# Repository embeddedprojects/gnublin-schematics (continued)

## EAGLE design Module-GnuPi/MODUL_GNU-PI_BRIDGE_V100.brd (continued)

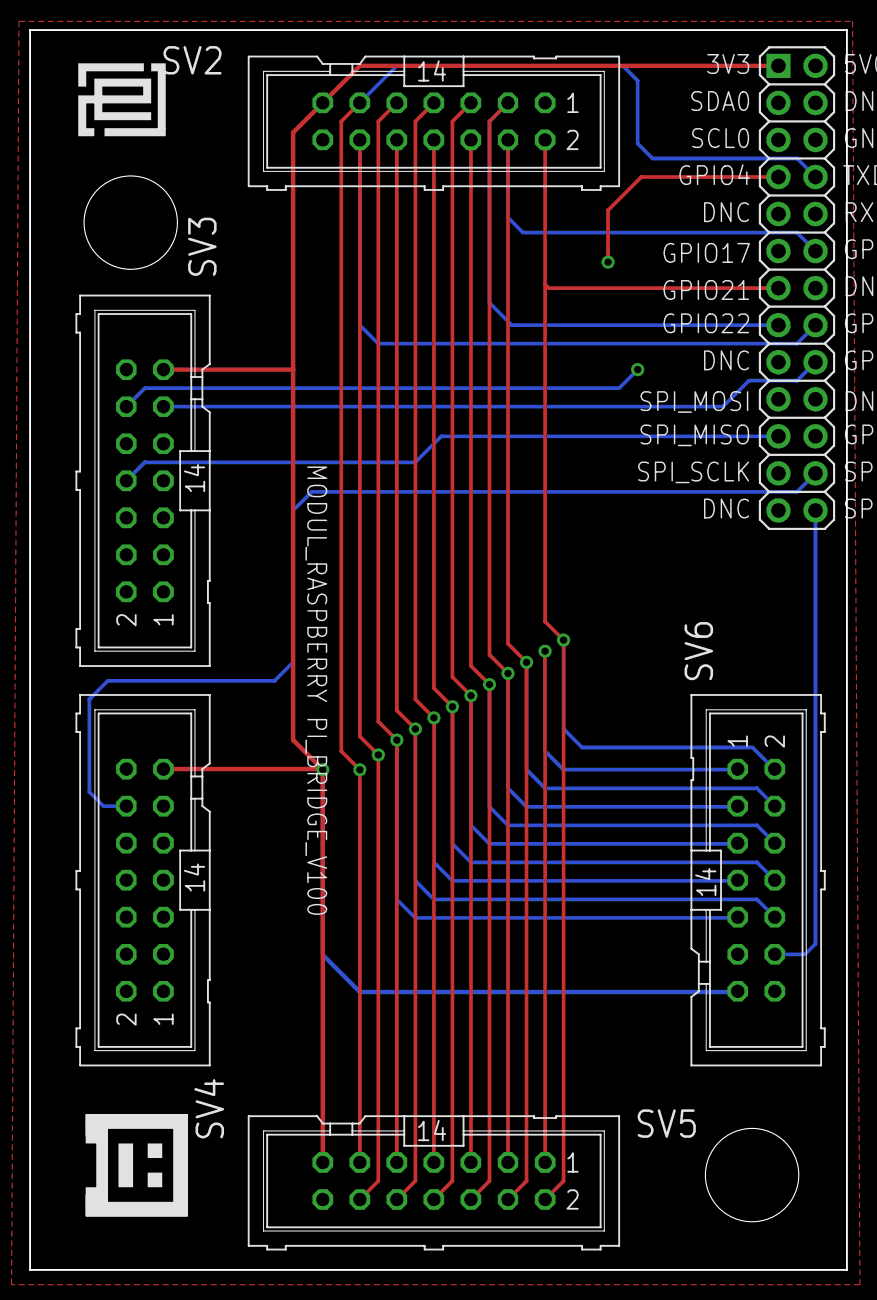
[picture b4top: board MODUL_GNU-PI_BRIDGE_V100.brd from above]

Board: 4 copper layers, 56.0 x 85.0 mm, 8 parts (0 on the bottom side), 20 nets.

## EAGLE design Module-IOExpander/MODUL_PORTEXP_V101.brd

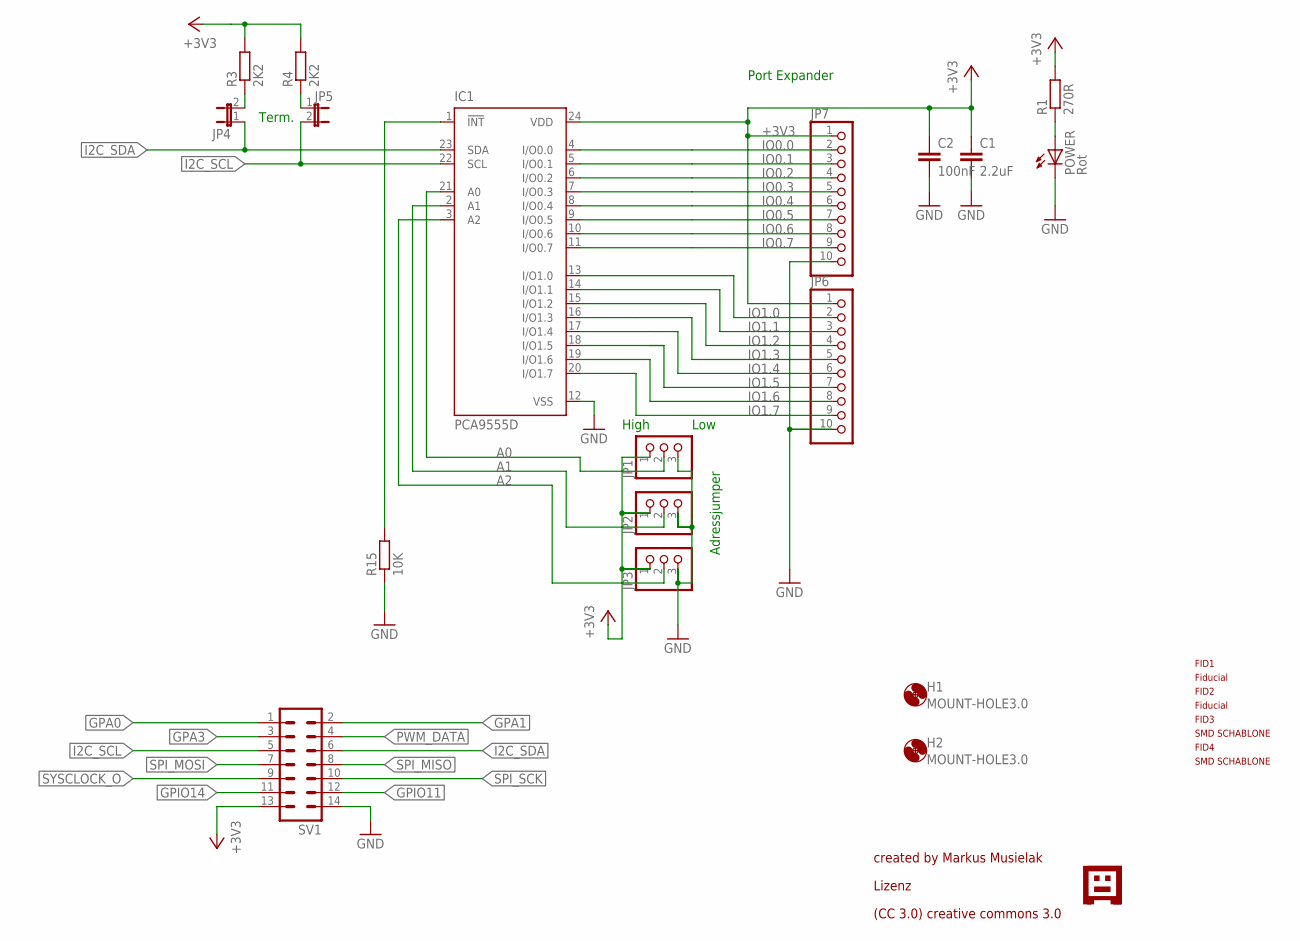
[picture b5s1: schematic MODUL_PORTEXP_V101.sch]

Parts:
C1: 2.2uF; C0805
C2: 100nF; C0805
FID1, FID2, FID3, FID4: PASSERMARKEN_FIDUCIAL
H1, H2: MOUNT-HOLE3.0; 3,0
IC1: PCA9555D; SO24
JP1, JP2, JP3: PINHD-1X3; 1X03
JP4, JP5: JP1E; JP1
JP6, JP7: PINHD-1X10; 1X10
POWER: Rot; CHIP-LED0805
R1: 270R; R0805
R3, R4: 2K2; R0805
R15: 10K; R0805
SV1: ML14
U$2: GNUBLINLOGOSIEB; GNUSIEBDRUCK

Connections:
!INT: IC1.1 (!INT), R15.2
+3V3: C1.1, C2.1, IC1.24 (VDD), JP1.1, JP2.1, JP3.1, JP6.1, JP7.1, R1.2, R3.2, R4.2, SV1.13
A0: IC1.21 (A0), JP1.2
A1: IC1.2 (A1), JP2.2
A2: IC1.3 (A2), JP3.2
GND: C1.2, C2.2, IC1.12 (VSS), JP1.3, JP2.3, JP3.3, JP6.10, JP7.10, POWER.C, R15.1, SV1.14
GPA0: SV1.1
GPA1: SV1.2
GPA3: SV1.3
GPIO11: SV1.12
GPIO14: SV1.11
I2C_SCL: IC1.22 (SCL), JP5.2, SV1.5
I2C_SDA: IC1.23 (SDA), JP4.1, SV1.6
IO0.0: IC1.4 (I/O0.0), JP7.2
IO0.1: IC1.5 (I/O0.1), JP7.3
IO0.2: IC1.6 (I/O0.2), JP7.4
IO0.3: IC1.7 (I/O0.3), JP7.5
IO0.4: IC1.8 (I/O0.4), JP7.6
IO0.5: IC1.9 (I/O0.5), JP7.7
IO0.6: IC1.10 (I/O0.6), JP7.8
IO0.7: IC1.11 (I/O0.7), JP7.9
IO1.0: IC1.13 (I/O1.0), JP6.2
IO1.1: IC1.14 (I/O1.1), JP6.3
IO1.2: IC1.15 (I/O1.2), JP6.4
IO1.3: IC1.16 (I/O1.3), JP6.5
IO1.4: IC1.17 (I/O1.4), JP6.6
IO1.5: IC1.18 (I/O1.5), JP6.7
IO1.6: IC1.19 (I/O1.6), JP6.8
IO1.7: IC1.20 (I/O1.7), JP6.9
unnamed: JP4.2, R3.1
unnamed: POWER.A, R1.1
unnamed: JP5.1, R4.1
PWM_DATA: SV1.4
SPI_MISO: SV1.8
SPI_MOSI: SV1.7
SPI_SCK: SV1.10
SYSCLOCK_O: SV1.9

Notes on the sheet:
Port Expander
Adressjumper
Term.
High
Low
created by Markus Musielak
Lizenz
(CC 3.0) creative commons 3.0

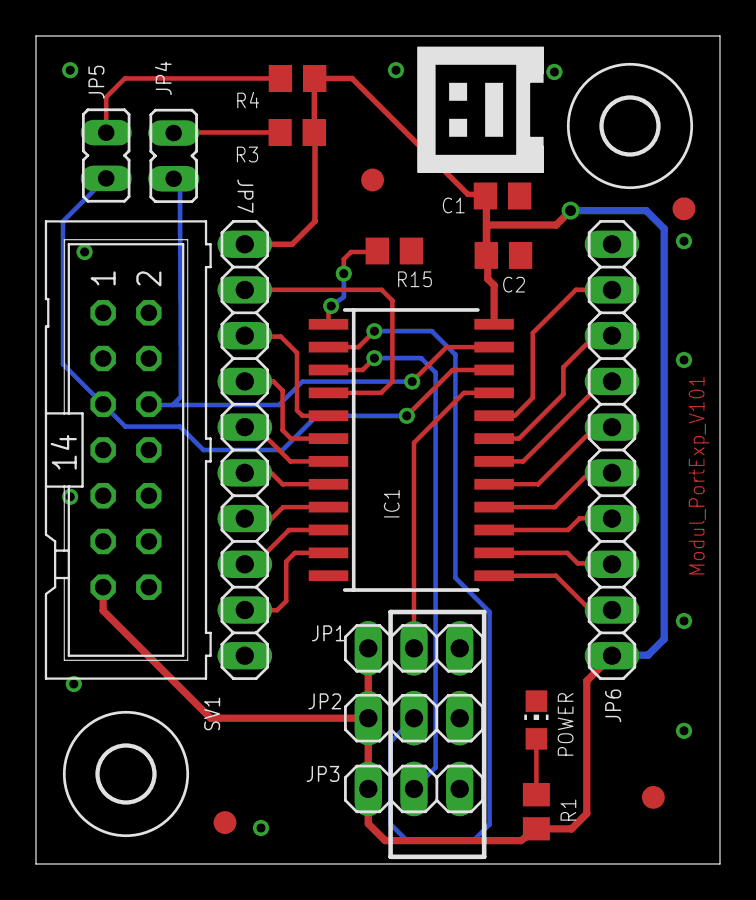
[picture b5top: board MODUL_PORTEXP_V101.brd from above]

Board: 2 copper layers, 38.0 x 46.0 mm, 23 parts (0 on the bottom side), 27 nets.

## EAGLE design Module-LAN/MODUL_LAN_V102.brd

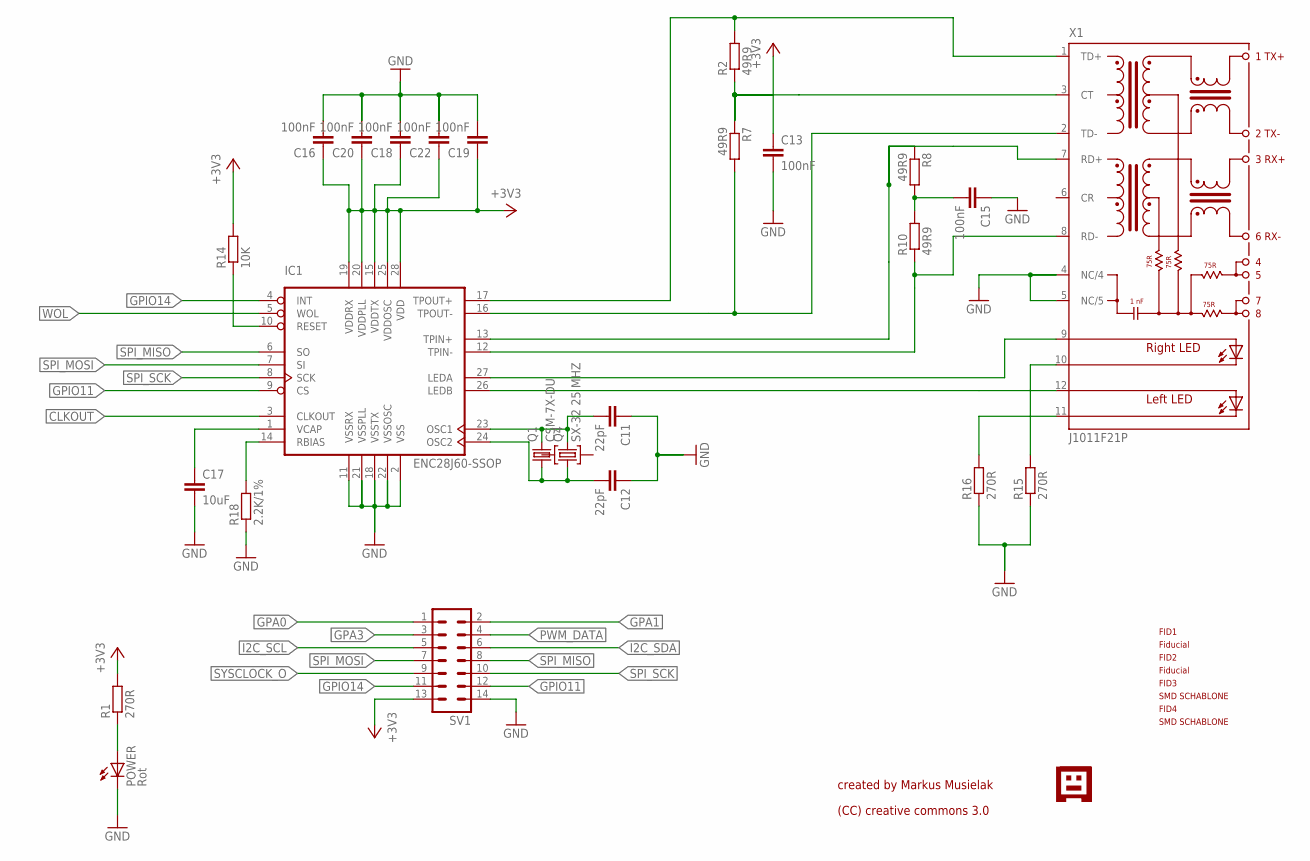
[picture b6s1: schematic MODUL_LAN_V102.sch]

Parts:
C11, C12: 22pF; C0805
C13, C15, C16, C18, C19, C20, C22: 100nF; C0805
C17: 10uF; C0805
FID1, FID2, FID3, FID4: PASSERMARKEN_FIDUCIAL
IC1: ENC28J60-SSOP; SSOP28; FARNELL 1084620
POWER: Rot; CHIP-LED0805
Q1: CSM-7X-DU
Q4: SX-32 25 MHZ; SX-32; FARNELL 1712841
R1, R15, R16: 270R; R0805
R2, R7, R8, R10: 49R9; R0805
R14: 10K; R0805
R18: 2.2K/1%; R0805
SV1: ML14
U$2: GNUBLINLOGOSIEB; GNUSIEBDRUCK
X1: J1011F21P; J1

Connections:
+3V3: C13.1, C16.1, C18.1, C19.1, C20.1, C22.1, IC1.15 (VDDTX), IC1.19 (VDDRX), IC1.20 (VDDPLL), IC1.25 (VDDOSC), IC1.28 (VDD), R1.2, R2.1, R7.1, R14.2, SV1.13, X1.3 (CT)
CLKOUT: IC1.3 (CLKOUT)
GND: C11.1, C12.1, C13.2, C15.1, C16.2, C17.2, C18.2, C19.2, C20.2, C22.2, IC1.2 (VSS), IC1.11 (VSSRX), IC1.18 (VSSTX), IC1.21 (VSSPLL), IC1.22 (VSSOSC), POWER.C, R15.1, R16.1, R18.1, SV1.14, X1.4 (NC/4), X1.5 (NC/5)
GPA0: SV1.1
GPA1: SV1.2
GPA3: SV1.3
GPIO11: IC1.9 (CS), SV1.12
GPIO14: IC1.4 (INT), SV1.11
I2C_SCL: SV1.5
I2C_SDA: SV1.6
LINKACT: R15.2, X1.10 (C-R)
unnamed: C15.2, R8.2, R10.2
unnamed: POWER.A, R1.1
unnamed: IC1.10 (RESET), R14.1
unnamed: C17.1, IC1.1 (VCAP)
unnamed: IC1.27 (LEDA), X1.9 (A-R)
unnamed: IC1.26 (LEDB), X1.12 (AL)
unnamed: IC1.14 (RBIAS), R18.2
PWM_DATA: SV1.4
RX+: IC1.13 (TPIN+), R8.1, X1.7 (RD+)
RX-: IC1.12 (TPIN-), R10.1, X1.8 (RD-)
SPEED: R16.2, X1.11 (C-L)
SPI_MISO: IC1.6 (SO), SV1.8
SPI_MOSI: IC1.7 (SI), SV1.7
SPI_SCK: IC1.8 (SCK), SV1.10
SYSCLOCK_O: SV1.9
TX+: IC1.17 (TPOUT+), R2.2, X1.1 (TD+)
TX-: IC1.16 (TPOUT-), R7.2, X1.2 (TD-)
WOL: IC1.5 (WOL)
XT1: C12.2, IC1.24 (OSC2), Q1.1, Q4.1
XT2: C11.2, IC1.23 (OSC1), Q1.2, Q4.3 (2)

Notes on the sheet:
created by Markus Musielak
(CC) creative commons 3.0

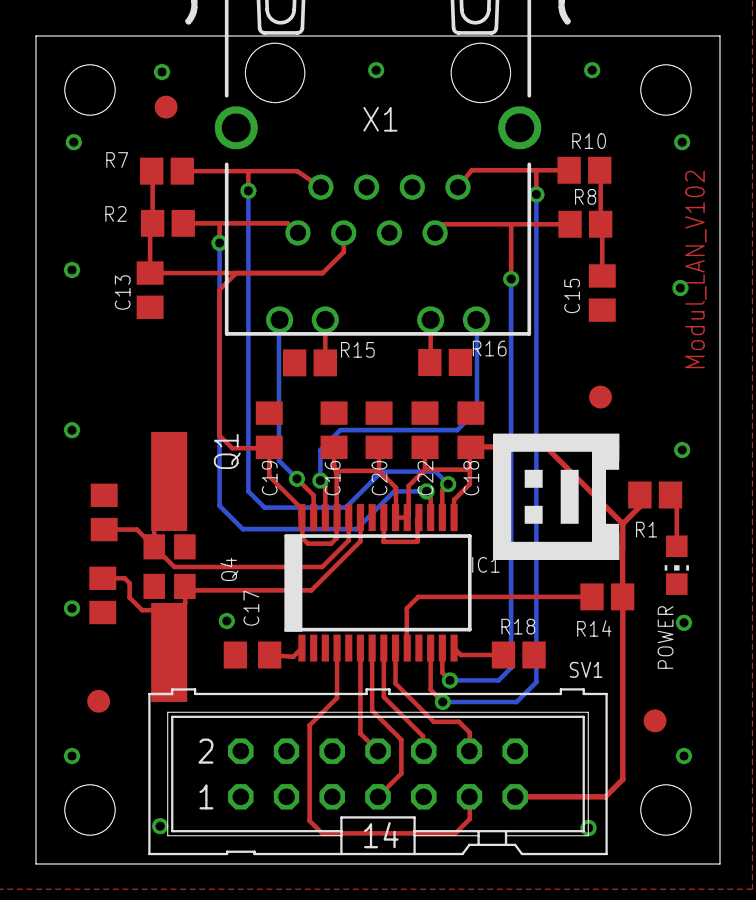
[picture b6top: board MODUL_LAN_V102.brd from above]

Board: 2 copper layers, 38.0 x 46.0 mm, 30 parts (0 on the bottom side), 22 nets.
